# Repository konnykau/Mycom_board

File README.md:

# Mycom_board_V2

マイコンボード V2

ブルーピルを刺すとうまく使えるようになる感じの基盤

電源供給はCANからでも5V以上の電源をvccにつなぐことでもできる（つなぐのはどっちかの方がいいのではないかという説）

LED0 : PC15

LED1 : PC14

LED2 : PC13

CAN_RX : PB8

CAN_TX : PB9

EMS : PA4

CANのLEDにつながってるところ : PA5

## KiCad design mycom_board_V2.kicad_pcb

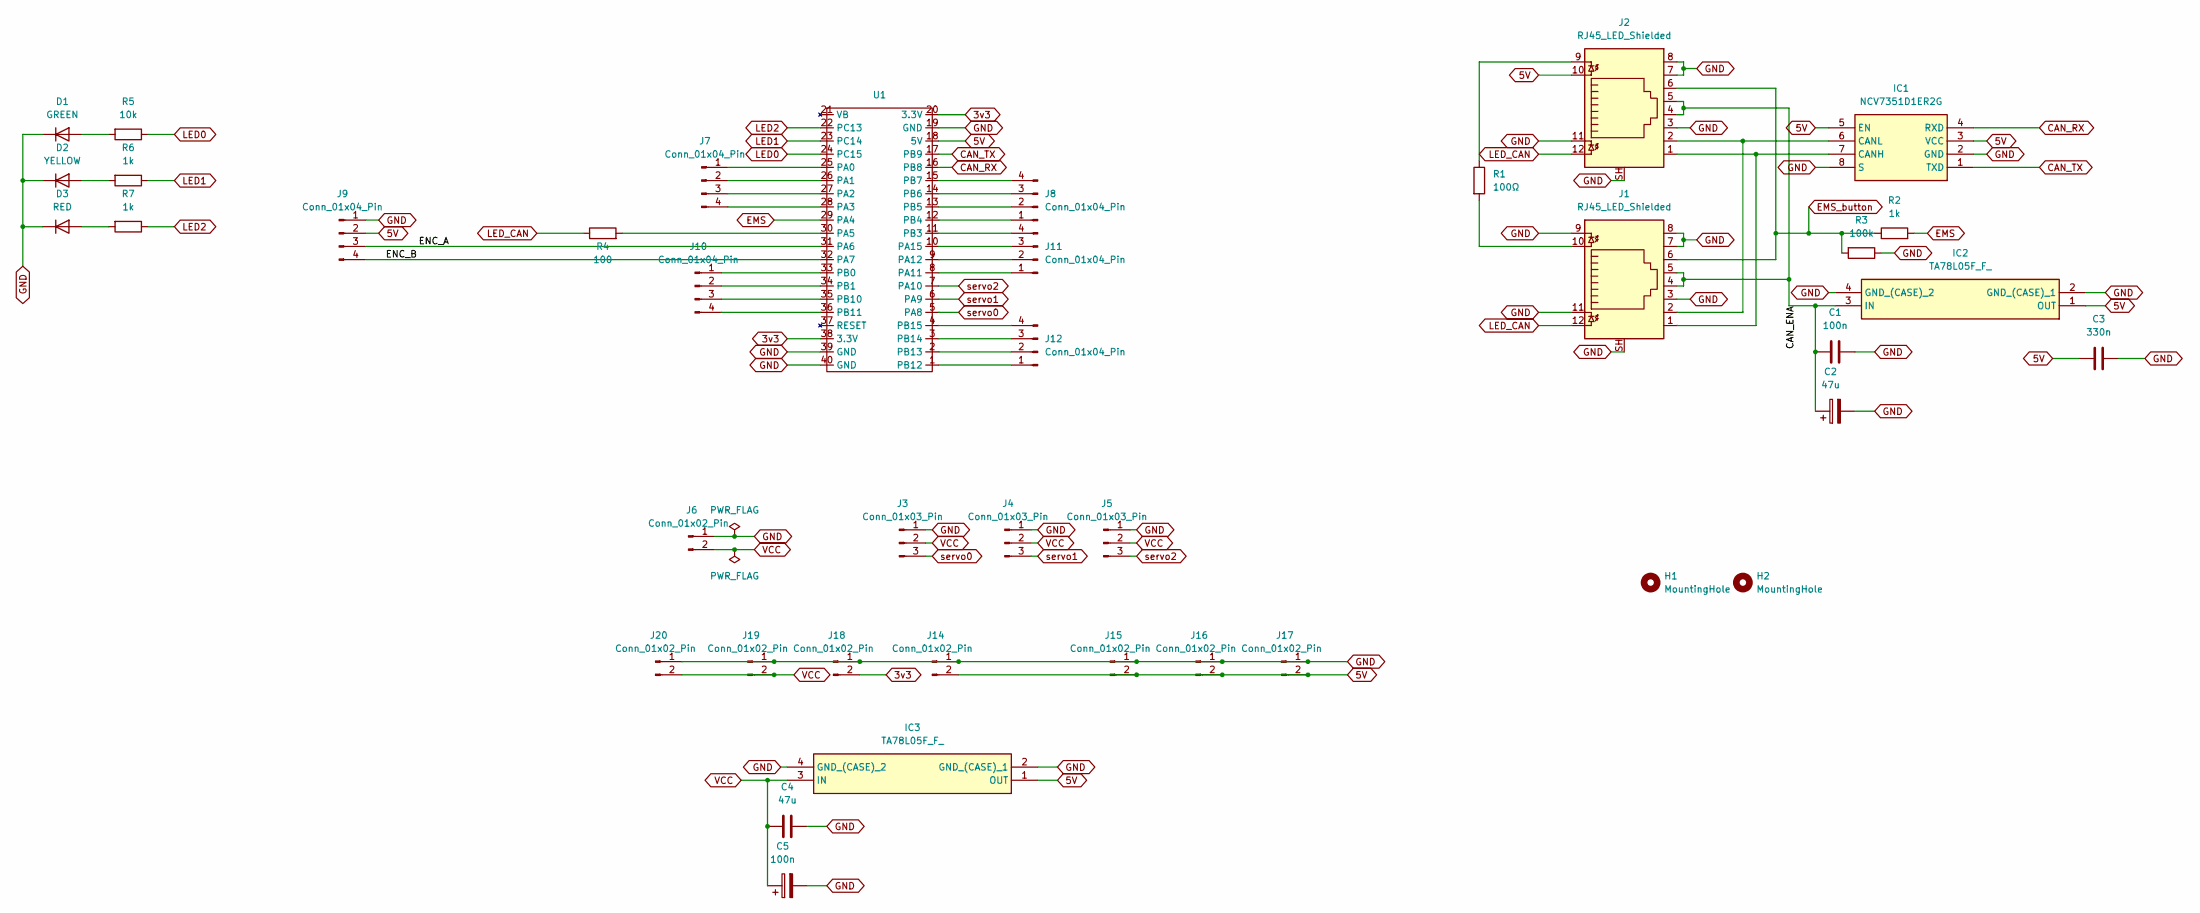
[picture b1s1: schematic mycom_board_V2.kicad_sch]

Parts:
C1: 100n; C_0603_1608Metric_Pad1.08x0.95mm_HandSolder
C2: 47u; big_cap
C3: 330n; C_0603_1608Metric_Pad1.08x0.95mm_HandSolder
C4: 47u; C_0603_1608Metric_Pad1.08x0.95mm_HandSolder
C5: 100n; big_cap
D1: GREEN; LED_0603_1608Metric_Pad1.05x0.95mm_HandSolder
D2: YELLOW; LED_0603_1608Metric_Pad1.05x0.95mm_HandSolder
D3: RED; LED_0603_1608Metric_Pad1.05x0.95mm_HandSolder
H1, H2: MountingHole; MountingHole_3.2mm_M3
IC1: NCV7351D1ER2G; Manufacturer_Part_Number NCV7351D1ER2G; Mouser Part Number 863-NCV7351D1ER2G
IC2, IC3: TA78L05F_F_; 4-PIN-HSOP; Manufacturer_Part_Number TA78L05F(F)
J1, J2: RJ45_LED_Shielded; RJ45_Amphenol_RJHSE538X
J3, J4, J5: Conn_01x03_Pin; PinHeader_1x03_P2.54mm_Vertical
J6, J14, J15, J16, J17, J18, J19, J20: Conn_01x02_Pin; PinHeader_1x02_P2.54mm_Vertical
J7, J8, J10, J11, J12: Conn_01x04_Pin; PinHeader_1x04_P2.54mm_Vertical
J9: Conn_01x04_Pin; encoder_connect
R1: 100Ω; R_0603_1608Metric_Pad0.98x0.95mm_HandSolder
R2, R6, R7: 1k; R_0603_1608Metric_Pad0.98x0.95mm_HandSolder
R3: 100k; R_0603_1608Metric_Pad0.98x0.95mm_HandSolder
R4: 100; R_0603_1608Metric_Pad0.98x0.95mm_HandSolder
R5: 10k; R_0603_1608Metric_Pad0.98x0.95mm_HandSolder
U1: YAAJ_BluePill_1

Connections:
3v3: J18.2, U1.20 (3.3V), U1.38 (3.3V)
5V: C3.1, IC1.3 (VCC), IC1.5 (EN), IC2.1 (OUT), IC3.1 (OUT), J2.10, J9.2, J14.2, J15.2, J16.2, J17.2, U1.18 (5V)
/CAN_ENA: C1.1, C2.1, IC2.3 (IN), J1.4, J1.5, J2.4, J2.5
/ENC_A: J9.3, U1.31 (PA6)
/ENC_B: J9.4, U1.32 (PA7)
CAN_RX: IC1.4 (RXD), U1.16 (PB8)
CAN_TX: IC1.1 (TXD), U1.17 (PB9)
EMS: R2.2, U1.29 (PA4)
EMS_button: J1.6, J2.6, R2.1, R3.2
GND: C1.2, C2.2, C3.2, C4.2, C5.2, D1.1 (K), D2.1 (K), D3.1 (K), IC1.2 (GND), IC1.8 (S), IC2.2 (GND_(CASE)_1), IC2.4 (GND_(CASE)_2), IC3.2 (GND_(CASE)_1), IC3.4 (GND_(CASE)_2), J1.3, J1.7, J1.8, J1.9, J1.11, J1.SH, J2.3, J2.7, J2.8, J2.11, J2.SH, J3.1, J4.1, J5.1, J6.1, J9.1, J14.1, J15.1, J16.1, J17.1, J18.1, J19.1, J20.1, R3.1, U1.19 (GND), U1.39 (GND), U1.40 (GND)
LED0: R5.1, U1.24 (PC15)
LED1: R6.1, U1.23 (PC14)
LED2: R7.1, U1.22 (PC13)
LED_CAN: J1.12, J2.12, R4.1
unnamed: D1.2 (A), R5.2
unnamed: D2.2 (A), R6.2
unnamed: D3.2 (A), R7.2
unnamed: IC1.7 (CANH), J1.1, J2.1
unnamed: IC1.6 (CANL), J1.2, J2.2
unnamed: J1.10, R1.2
unnamed: J2.9, R1.1
unnamed: J7.1, U1.25 (PA0)
unnamed: J7.2, U1.26 (PA1)
unnamed: J7.3, U1.27 (PA2)
unnamed: J7.4, U1.28 (PA3)
unnamed: J8.1, U1.12 (PB4)
unnamed: J8.2, U1.13 (PB5)
unnamed: J8.3, U1.14 (PB6)
unnamed: J8.4, U1.15 (PB7)
unnamed: J10.1, U1.33 (PB0)
unnamed: J10.2, U1.34 (PB1)
unnamed: J10.3, U1.35 (PB10)
unnamed: J10.4, U1.36 (PB11)
unnamed: J11.1, U1.8 (PA11)
unnamed: J11.2, U1.9 (PA12)
unnamed: J11.3, U1.10 (PA15)
unnamed: J11.4, U1.11 (PB3)
unnamed: J12.1, U1.1 (PB12)
unnamed: J12.2, U1.2 (PB13)
unnamed: J12.3, U1.3 (PB14)
unnamed: J12.4, U1.4 (PB15)
unnamed: R4.2, U1.30 (PA5)
VCC: C4.1, C5.1, IC3.3 (IN), J3.2, J4.2, J5.2, J6.2, J19.2, J20.2
servo0: J3.3, U1.5 (PA8)
servo1: J4.3, U1.6 (PA9)
servo2: J5.3, U1.7 (PA10)

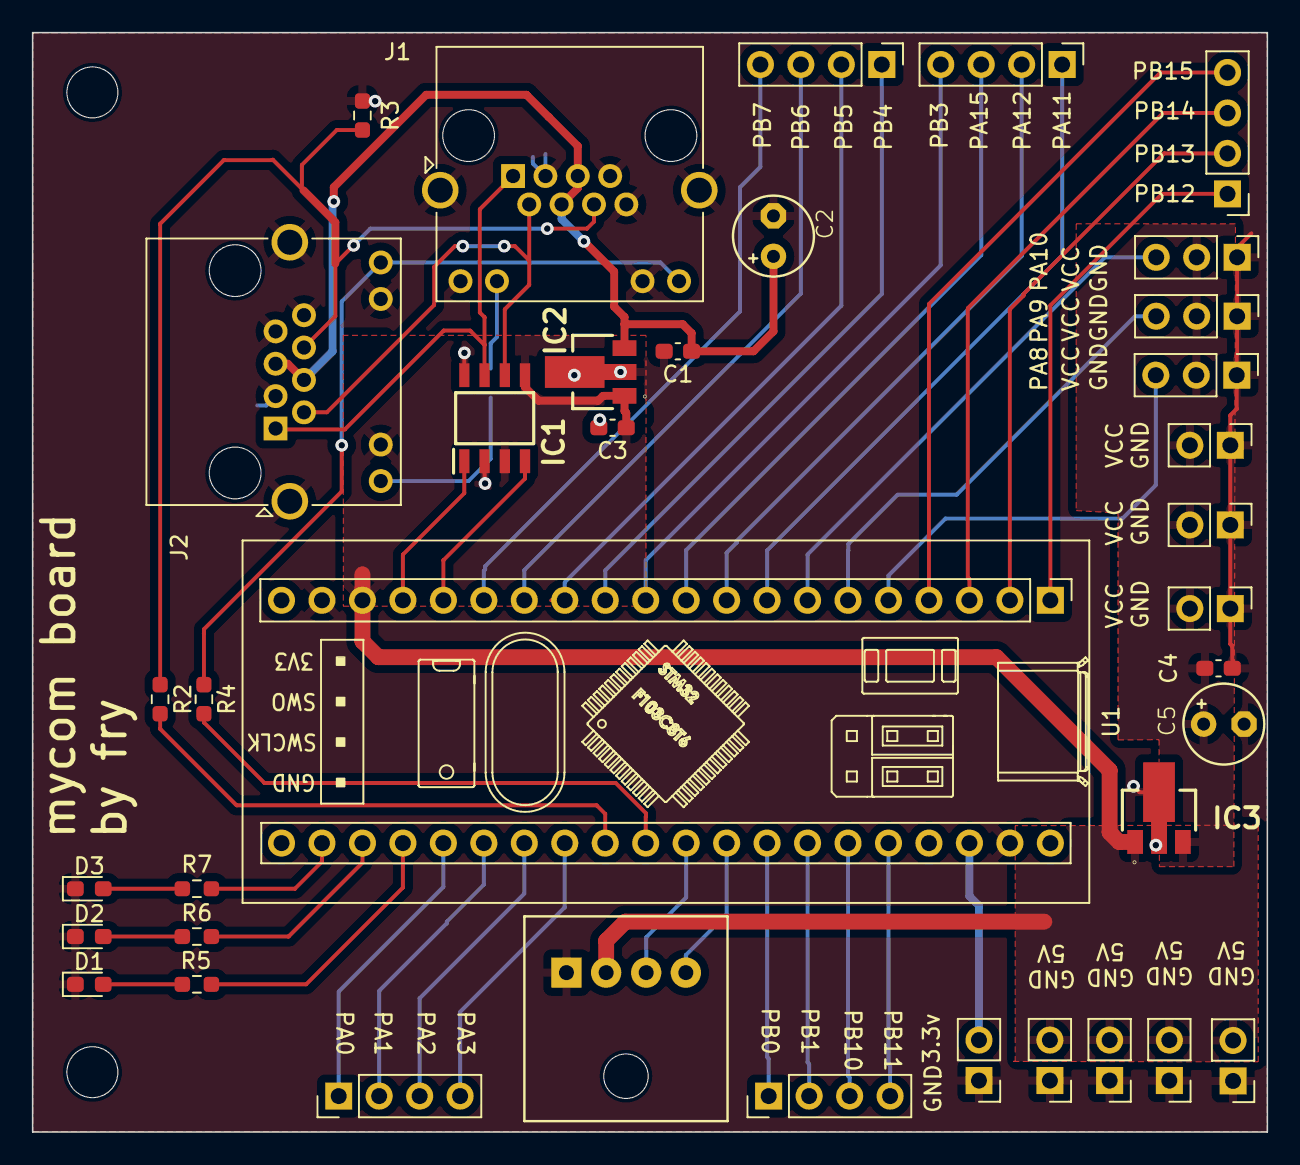
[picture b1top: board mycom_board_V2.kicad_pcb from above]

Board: 2 copper layers, 77.5 x 69.0 mm, 40 parts (1 on the bottom side), 46 nets.

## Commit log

2024-02-08 Add files via upload
    いろいろ変えた
